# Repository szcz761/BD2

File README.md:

# BD2
Robot klasy minisumo tworzony przez: Szymona Czaje.
Na podstawie robota: Biała-Dama współtworzonego z Markiem Żyśko.

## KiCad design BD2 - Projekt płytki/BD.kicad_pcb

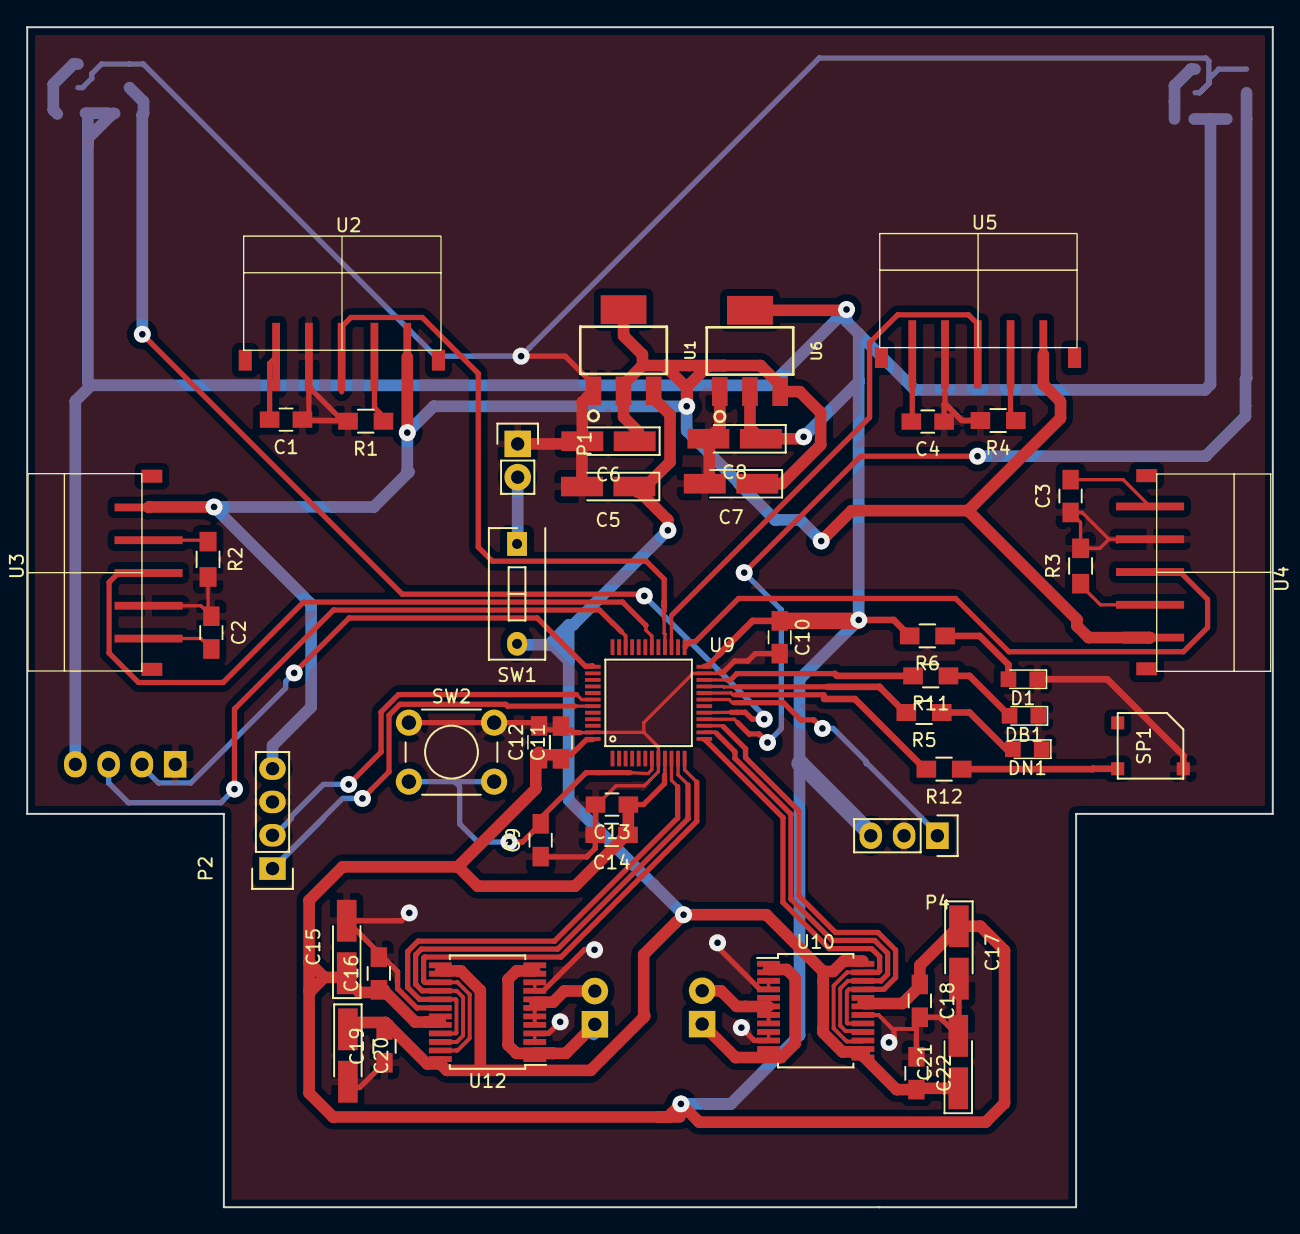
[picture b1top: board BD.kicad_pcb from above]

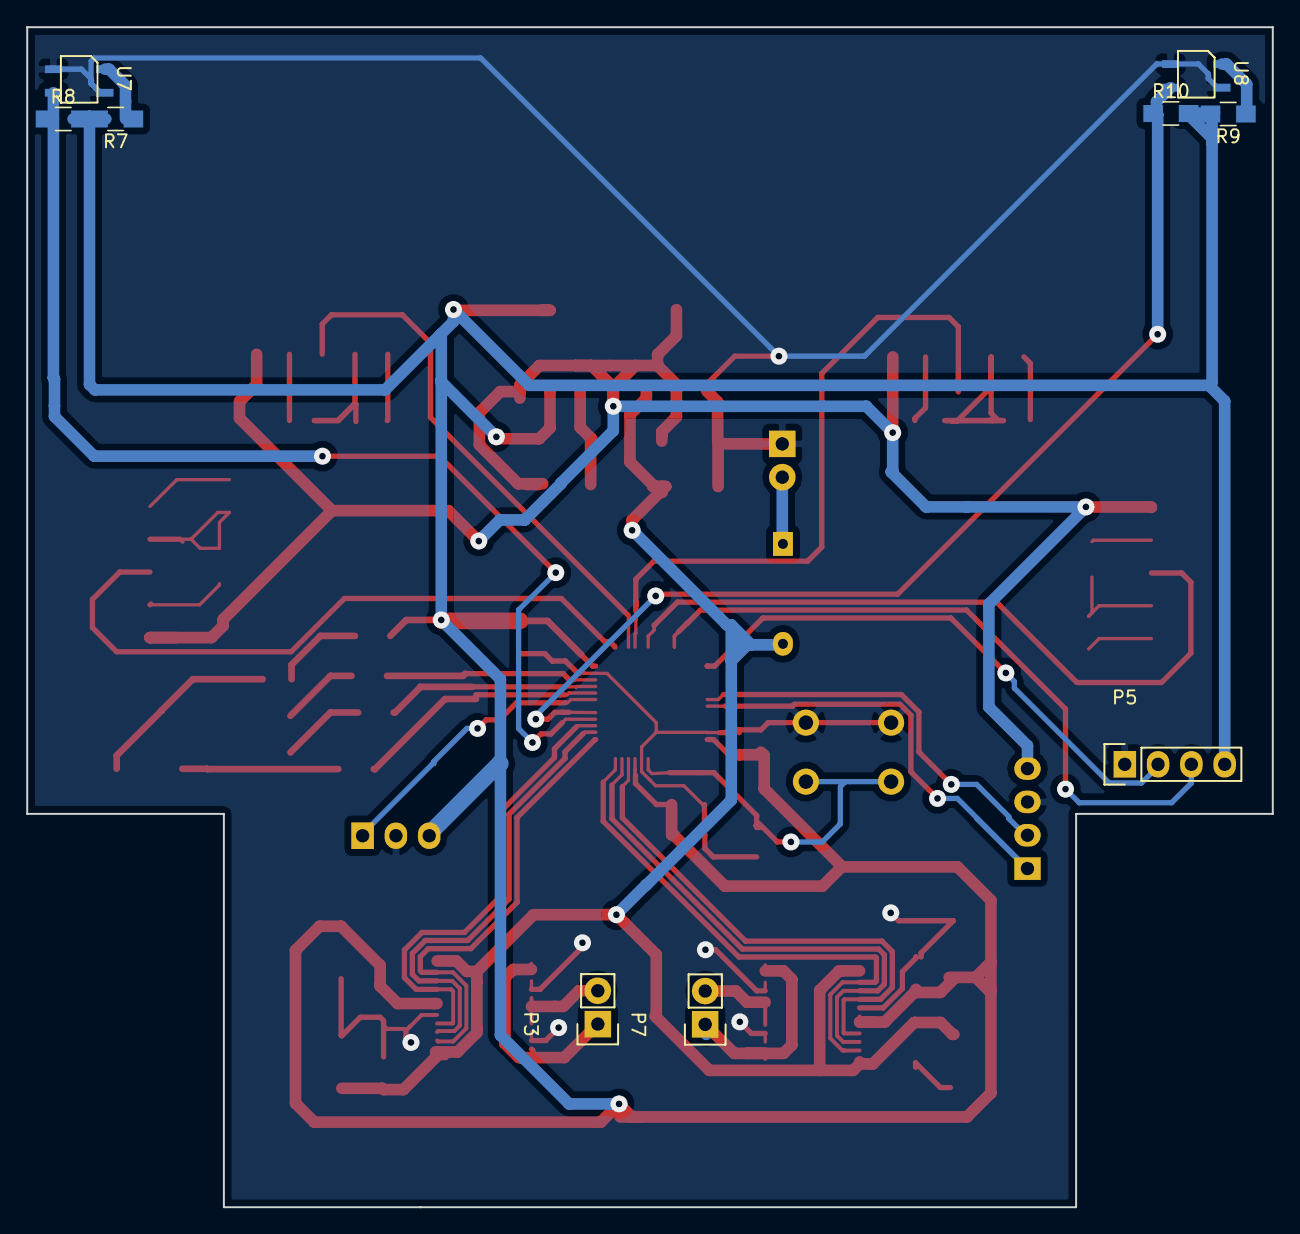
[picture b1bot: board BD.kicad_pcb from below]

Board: 2 copper layers, 95.0 x 90.0 mm, 57 parts (9 on the bottom side), 44 nets.

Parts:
C1, C2, C3, C4: 1 uF; C_0805_HandSoldering
C5, C6, C7, C8, C15, C17, C20, C21: 10uF; Tantalum_Case-A_EIA-3216-18_Hand
C9, C16, C18, C19, C22: 0.1uF; C_0805_HandSoldering
C10, C11: 100nF; C_0805_HandSoldering
C12: 4.7uF; C_0805_HandSoldering
C13: 1uF; C_0805_HandSoldering
C14: 10nF; C_0805_HandSoldering
D1: LED0; LED_0805
DB1: LED1; LED_0805
DN1: LED2; LED_0805
P1: bateria 7.4 V; Socket_Strip_Straight_1x02
P2: HC-06 (BT); Socket_Strip_Straight_1x04
P3: SILNIK1; Socket_Strip_Straight_1x02
P4: Modol startujacy; Socket_Strip_Straight_1x03
P5: PROGRAMAT; Socket_Strip_Straight_1x04
P7: SILNIK2; Socket_Strip_Straight_1x02
R1, R2, R3, R4: 1 Ohm; R_0805_HandSoldering
R5, R6, R11, R12: 100 Ohm; R_0805_HandSoldering
R7, R9: 220 Ohm; R_0805_HandSoldering
R8, R10: 10 kOhm; R_0805_HandSoldering
SP1: HCM1201X (BUZZER); BUZZER_SMD
SW1: SPST; SW_DIP_x1_Slide
SW2: SW_PUSH; SW_PUSH_6mm
U1, U6: LM1117; LM1117_SOT223
U2, U3, U4, U5: SHARP_40CM; GP2Y0D340K
U7, U8: KTIR0711S
U9: STM32F051C8Tx; STM32F051C8T6
U10, U12: TB6612

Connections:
+3V3: C8.1, C10.1, C11.1, C12.1, C13.1, C14.1, C15.1, C16.1, C17.1, C18.1, P4.3, P5.4, R6.2, R7.2, R8.2, R9.2, R10.2, U6.2, U9.9, U9.24, U9.48, U10.19, U10.20, U12.19, U12.20
+5V: C6.1, C7.1, P2.4, U1.2, U2.1, U3.1, U4.1, U5.1, U6.1
BT1: P2.2, U9.42
BT2: P2.1, U9.43
BUZZ: R12.2, U9.20
GND: C1.1, C2.1, C3.1, C4.1, C5.2, C6.2, C7.2, C8.2, C9.1, C10.2, C11.2, C12.2, C13.2, C14.2, C15.2, C16.2, C17.2, C18.2, C19.1, C20.2, C21.2, C22.1, D1.1, DB1.1, DN1.1, P1.1, P2.3, P4.2, P5.1, R1.2, R2.2, R3.2, R4.2, SP1.1, SW2.1, U1.3, U2.4, U3.4, U4.4, U5.4, U6.3, U7.2, U7.3, U8.2, U8.3, U9.8, U9.23, U9.47, U10.3, U10.4, U10.9, U10.10, U10.18, U12.3, U12.4, U12.9, U12.10, U12.18
KTIR1: R8.1, U7.4, U9.16
KTIR2: R10.1, U8.4, U9.17
LED1: R11.2, U9.22
LED2: R5.2, U9.21
MOD_START: P4.1, U9.19
unnamed: C1.2, U2.5
unnamed: C2.2, U3.5
unnamed: C3.2, U4.5
unnamed: C4.2, U5.5
unnamed: D1.2, R6.1
unnamed: DB1.2, R11.1
unnamed: DN1.2, R5.1
unnamed: P1.2, SW1.1
unnamed: P3.1, U10.1, U10.2, U10.11, U10.12
unnamed: P3.2, U10.5, U10.6, U10.7, U10.8
unnamed: P7.1, U12.1, U12.2, U12.11, U12.12
unnamed: P7.2, U12.5, U12.6, U12.7, U12.8
unnamed: R1.1, U2.2
unnamed: R2.1, U3.2
unnamed: R3.1, U4.2
unnamed: R4.1, U5.2
unnamed: R7.1, U7.1
unnamed: R9.1, U8.1
unnamed: R12.1, SP1.2
PROG1: P5.3, U9.34
PROG2: P5.2, U9.37
RESET: C9.2, SW2.2, U9.7
S1/IN1: U9.15, U10.17, U10.21
S1/IN2: U9.14, U10.16, U10.22
S1/PWM: U9.13, U10.15, U10.23
S2/IN1: U9.10, U12.17, U12.21
S2/IN2: U9.11, U12.16, U12.22
S2/PWM: U9.12, U12.15, U12.23
SHARP1: U4.3, U9.25
SHARP2: U5.3, U9.27
SHARP3: U2.3, U9.28
SHARP4: U3.3, U9.30
VCC: C5.1, C19.2, C20.1, C21.1, C22.2, SW1.2, U1.1, U10.13, U10.14, U10.24, U12.13, U12.14, U12.24

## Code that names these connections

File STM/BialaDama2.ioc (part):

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Mcu.Name=STM32F051C8Tx
Mcu.Package=LQFP48
Mcu.UserName=STM32F051C8Tx
PA0.GPIOParameters=GPIO_Label
PA0.GPIO_Label=S2/IN1
PA0.Signal=GPIO_Output
PA1.GPIOParameters=GPIO_Label
PA1.GPIO_Label=S2/IN2
PA1.Signal=GPIO_Output
PA13.GPIOParameters=GPIO_Label
PA13.GPIO_Label=PROG1
PA13.Mode=Serial_Wire
PA13.Signal=SYS_SWDIO
PA14.GPIOParameters=GPIO_Label
PA14.GPIO_Label=PROG2
PA14.Mode=Serial_Wire
PA14.Signal=SYS_SWCLK
PA2.GPIOParameters=GPIO_Label
PA2.GPIO_Label=S2/PWM
PA2.Signal=S_TIM2_CH3
PA3.GPIOParameters=GPIO_Label
PA3.GPIO_Label=S1/PWM
PA3.Signal=S_TIM2_CH4
PA4.GPIOParameters=GPIO_Label
PA4.GPIO_Label=S1/IN2
PA4.Signal=GPIO_Output
PA5.GPIOParameters=GPIO_Label
PA5.GPIO_Label=S1/IN1
PA5.Signal=GPIO_Output
PA6.GPIOParameters=GPIO_Label
PA6.GPIO_Label=KTIR1
PA6.Mode=IN6
PA6.Signal=ADC_IN6
PA7.GPIOParameters=GPIO_Label
PA7.GPIO_Label=KTIR2
PA7.Mode=IN7
PA7.Signal=ADC_IN7
PA9.GPIOParameters=GPIO_PuPd,GPIO_Label
PA9.GPIO_Label=SHARP4
PA9.GPIO_PuPd=GPIO_PULLDOWN
PA9.Signal=GPIO_Input
PB1.GPIOParameters=GPIO_Label
PB1.GPIO_Label=MOD_START
PB1.Signal=GPIO_Input
PB10.GPIOParameters=GPIO_Label
PB10.GPIO_Label=LED2
PB10.Signal=GPIO_Output
PB11.GPIOParameters=GPIO_Label
PB11.GPIO_Label=LED1
PB11.Signal=GPIO_Output
PB12.GPIOParameters=GPIO_PuPd,GPIO_Label
PB12.GPIO_Label=SHARP1
PB12.GPIO_PuPd=GPIO_PULLDOWN
PB12.Signal=GPIO_Input
PB14.GPIOParameters=GPIO_PuPd,GPIO_Label
PB14.GPIO_Label=SHARP2
PB14.GPIO_PuPd=GPIO_PULLDOWN
PB14.Signal=GPIO_Input
PB15.GPIOParameters=GPIO_PuPd,GPIO_Label
PB15.GPIO_Label=SHARP3
PB15.GPIO_PuPd=GPIO_PULLDOWN
PB15.Signal=GPIO_Input
PB2.GPIOParameters=GPIO_Label
PB2.GPIO_Label=BUZZ
PB2.Signal=GPIO_Output
PB6.GPIOParameters=GPIO_Label
PB6.GPIO_Label=BT2
PB6.Mode=Asynchronous
PB6.Signal=USART1_TX
PB7.GPIOParameters=GPIO_Label
PB7.GPIO_Label=BT1
PB7.Mode=Asynchronous
PB7.Signal=USART1_RX
RCC.SYSCLKFreq_VALUE=48000000
RCC.SYSCLKSource=RCC_SYSCLKSOURCE_PLLCLK
